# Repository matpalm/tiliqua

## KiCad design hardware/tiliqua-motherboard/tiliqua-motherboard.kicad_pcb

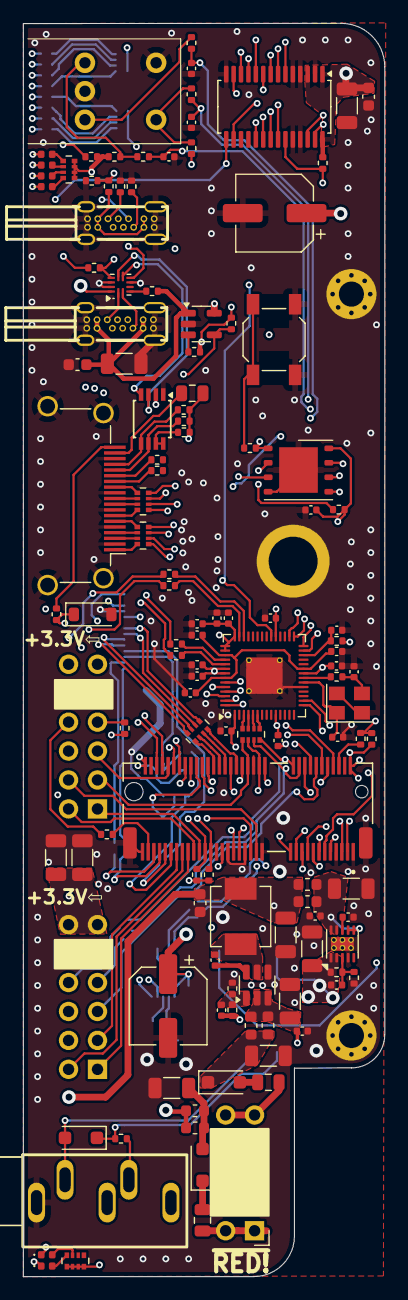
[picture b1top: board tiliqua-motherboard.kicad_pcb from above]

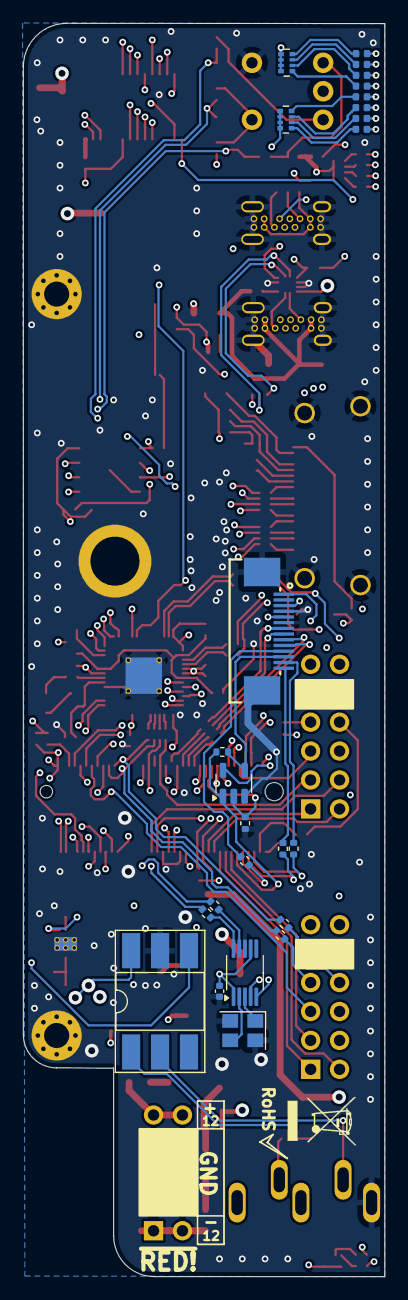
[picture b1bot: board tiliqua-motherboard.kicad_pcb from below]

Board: 6 copper layers, 31.7 x 110.0 mm, 153 parts (25 on the bottom side), 168 nets.

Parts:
C1, C2, C3, C4, C5, C6, C7, C8, C9, C10, C13, C14, C36: 0.1uF; C_0402_1005Metric
C11, C12: 2.2uF; C_0402_1005Metric
C15, C16: 15pF; C_0402_1005Metric
C17, C25, C28, C30: 100nF; C_0402_1005Metric
C18, C39, C40, C41: 10n; C_0402_1005Metric
C19, C20, C22, C23, C24, C26, C29, C32, C38, C42: 22uF; C_1206_3216Metric
C21, C33: 100uF/10V; CP_Elec_6.3x5.4
C27, C34, C43: 100nF; C_0603_1608Metric
C31: 100pF; C_0402_1005Metric
D1, D2, D3: 1N4007FL; D_SOD-123F
D4: 3V6; D_SOD-123
D5, D6, D7, D8, D13, D14, D16: LED 0402 GREEN; LED_0402_1005Metric
D9, D10, D11, D12, D17, D18, D20: LED 0402 RED; LED_0402_1005Metric
F1: 16V 350mA; Fuse_0805_2012Metric
F2: 15V 200mA; Fuse_0805_2012Metric
F3: 15V 50mA; Fuse_0805_2012Metric
H1, H2: MountingHole; MountingHole_2.2mm_M2_Pad_Via
H3: MountingHole; mounting_hole
J1: Conn_01x15; FFC_0.5-14P_CTXJ-H2.0_1
J2, J3: Conn_02x06_Top_Bottom; PinSocket_2x06_P2.54mm_Horizontal
J4: AUDIO-TH_PJ-325M
J5, J7: USB_C_Receptacle_USB2.0_14P; USB-C-TH_U264-141N-4BAC10
J6: CONN 2x5 P=2.54mm; PinHeader_2x05_P2.54mm_Horizontal
J8: MICROMOD-2222; TE_21992304
J10: DVI_GPDI; HDMI_A_Amphenol_10029449-x01xLF_Horizontal
L1, L2, L4, L5, L6, L7: FERRITE; L_0603_1608Metric
L3: 10uH 2A; L_Vishay_IHLP-2020
R1, R2, R9, R19, R25, R32: 4K7; R_0402_1005Metric
R3, R4, R13, R14, R21, R22, R23, R27, R28, R29, R30, R33, R45: 10K; R_0402_1005Metric
R5, R15: 1K; R_0402_1005Metric
R6, R7: 27R; R_0402_1005Metric
R8: 100R; R_0402_1005Metric
R10, R16: 220R; R_0402_1005Metric
R11, R12: 5.1K; R_0402_1005Metric
R17: 157K (158K); R_0402_1005Metric
R18: 30K; R_0402_1005Metric
R20: 900K (910K); R_0402_1005Metric
R24: 18K; R_0402_1005Metric
R26, R31: 549; R_0402_1005Metric
R34, R35, R36, R37, R38, R39, R40, R41, R47, R48, R49: 33R; R_0402_1005Metric
R42: 1K15; R_0402_1005Metric
R43: 3K57; R_0402_1005Metric
R44: 200K; R_0402_1005Metric
R46: 0R; R_0402_1005Metric
RN1, RN2, RN3, RN4, RN6, RN7: 220R; R_Array_Convex_4x0402
RN5, RN8: 33R; R_Array_Convex_4x0402
SW2: SW_Tactile_SPST; SW_SPST_SKQG_WithStem
SW3: RotaryEncoder_Switch; RotaryEncoder_Bourns_Horizontal_PEC09-2xxxF-Sxxxx
U2: RP2040(QFN-56_7x7mm_P0.4mm); QFN-56-1EP_7x7mm_P0.4mm_EP3.2x3.2mm_ThermalVias
U3: PCA9306DP; TSSOP-8_3x3mm_P0.65mm
U4: H11L1SR2M; DIP-6_W8.89mm_SMDSocket_LongPads
U5: AP63200WU; TSOT-23-6
U6: 74AUC1G79; SOT-23-5
U7: PCA9635 LED DRIVER; TSSOP-28_4.4x9.7mm_P0.65mm
U8: TUSB322I; Texas_X2QFN-12_1.6x1.6mm_P0.4mm
U9: AP2161W; SOT-23-5
U10: TPS7A91; Texas_S-PDSO-N10_EP1.2x2mm_ThermalVias
U11: Si5351A-B-GT; MSOP-10_3x3mm_P0.5mm
U12: W25Q128JVP; WSON-8-1EP_6x5mm_P1.27mm_EP3.4x4mm
Y1: Crystal_GND24_Small; Crystal_SMD_3225-4Pin_3.2x2.5mm
Y2: 25MHz AMB8G; Crystal_SMD_3225-4Pin_3.2x2.5mm

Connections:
+3V3: C1.2, C3.1, C4.1, C5.1, C6.1, C7.1, C8.1, C9.1, C10.1, C11.1, C18.2, C21.1, C22.1, C24.1, C32.1, C33.1, C36.1, C42.1, C43.1, J1.5, J2.6, J2.12, J3.6, J3.12, J8.2 (3.3V), J8.74 (3.3V), R1.2, R2.2, R3.1, R4.1, R13.1, R14.1, R15.2, R19.2, R21.1, R27.1, R32.2, R33.1, R43.1, RN1.1 (R1.1), RN1.2 (R2.1), RN1.3 (R3.1), RN1.4 (R4.1), RN2.1 (R1.1), RN2.2 (R2.1), RN2.3 (R3.1), RN2.4 (R4.1), RN3.1 (R1.1), RN3.2 (R2.1), RN3.3 (R3.1), RN3.4 (R4.1), RN4.1 (R1.1), RN4.2 (R2.1), RN4.3 (R3.1), RN4.4 (R4.1), U2.1 (IOVDD), U2.10 (IOVDD), U2.22 (IOVDD), U2.33 (IOVDD), U2.42 (IOVDD), U2.43 (ADC_AVDD), U2.44 (VREG_VIN), U2.48 (USB_VDD), U2.49 (IOVDD), U3.2 (VREF1), U4.6, U6.5 (VCC), U7.1 (A0), U7.3 (A2), U7.28 (VDD), U10.1 (OUT), U10.2 (OUT), U11.1 (VDD), U11.7 (VDDO), U12.8 (VCC)
+5V: C31.2, C34.1, C38.1, F3.2, L3.2, L4.2, L5.2, R9.2, R17.2, R25.2, R44.1, U8.12 (VDD), U9.5 (IN)
+12V: C23.1, C25.1, J1.3, L1.1, L6.2, U5.2 (EN), U5.3 (IN)
-12V: J1.1, L2.1, L7.2
/gpdi/CONN_CK+: J10.10 (CK+), RN7.2 (R2.1)
/gpdi/CONN_CK-: J10.12 (CK-), RN7.1 (R1.1)
/gpdi/CONN_D0+: J10.7 (D0+), RN7.4 (R4.1)
/gpdi/CONN_D0-: J10.9 (D0-), RN7.3 (R3.1)
/gpdi/CONN_D1+: J10.4 (D1+), RN6.2 (R2.1)
/gpdi/CONN_D1-: J10.6 (D1-), RN6.1 (R1.1)
/gpdi/CONN_D2+: J10.1 (D2+), RN6.4 (R4.1)
/gpdi/CONN_D2-: J10.3 (D2-), RN6.3 (R3.1)
/pmod_audio/PDN: J1.12, R46.1, U6.4 (Q)
/rp2040_jtag/I2C0_SCL: R40.1, U2.41 (GPIO29/ADC3/SPI1_CSn/UART0_RX/I2C0_SCL/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)
/rp2040_jtag/I2C0_SDA: R41.1, U2.40 (GPIO28/ADC2/SPI1_RX/UART0_TX/I2C0_SDA/P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)
/rp2040_jtag/RP2040_USB_D+: J5.A6 (D+), J5.B6 (D+), R7.1
/rp2040_jtag/RP2040_USB_D-: J5.A7 (D-), J5.B7 (D-), R6.1
/rp2040_jtag/RP2040_USB_VBUS: J5.A4 (VBUS), J5.A9 (VBUS), J5.B4 (VBUS), J5.B9 (VBUS), R23.2
/rp2040_jtag/SPI0_CSn: RN8.8 (R1.2), U2.3 (GPIO1/SPI0_CSn/UART0_RX/I2C0_SCL/PWM0_B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)
/rp2040_jtag/SPI0_RX: RN8.5 (R4.2), U2.6 (GPIO4/SPI0_RX/UART1_TX/I2C0_SDA/PWM2_A/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)
/rp2040_jtag/SPI0_SCK: RN8.7 (R2.2), U2.4 (GPIO2/SPI0_SCK/UART0_CTS/I2C1_SDA/PWM1_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)
/rp2040_jtag/SPI0_TX: RN8.6 (R3.2), U2.5 (GPIO3/SPI0_TX/UART0_RTS/I2C1_SCL/PWM1_B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)
/usbc/~USB_VBUS_FLG: R27.2, U9.3 (~FLG)
ECP5_M10_TDO: J8.23 (SWDIO), U2.28 (GPIO17/SPI0_CSn/UART0_RX/I2C0_SCL/PWM0_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)
ECP5_R11_TDI: J8.18 (D1/CAM_TRIG), U2.27 (GPIO16/SPI0_RX/UART0_TX/I2C0_SDA/PWM0_A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)
ECP5_T10_TCK: J8.10 (D0), U2.29 (GPIO18/SPI0_SCK/UART0_CTS/I2C1_SDA/PWM1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)
ECP5_T11_TMS: J8.21 (SWDCK), U2.30 (GPIO19/SPI0_TX/UART0_RTS/I2C1_SCL/PWM1_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)
ENC_A: C41.1, J8.8 (G11), R29.2
ENC_B: C40.1, J8.12 (I2C_SDA), R30.2
ENC_S: C39.1, J8.43 (CAN-TX), R22.2
EX1_1: J3.1, J8.55 (SPI_~CS)
EX1_2: J3.2, J8.38 (A1), RN8.1 (R1.1)
EX1_3: J3.3, J8.66 (SDIO_DATA1)
EX1_4: J8.41 (CAN-RX), R39.1
EX1_7: J3.7, J8.57 (SPI_SCK)
EX1_8: J3.8, J8.35 (USBHOST_D+)
EX1_9: J3.9, J8.34 (A0), RN8.2 (R2.1)
EX1_10: J8.73 (G5/BUS5), R38.2
EX2_1: J2.1, J8.59 (SPI_SDO)
EX2_2: J2.2, J8.63 (G10/ADC_D+/CAM_VSYNC)
EX2_3: J2.3, J8.14 (I2C_SCL)
EX2_4: J8.20 (RX2), R37.1, RN8.3 (R3.1)
EX2_7: J2.7, J8.61 (SPI_SDI)
EX2_8: J2.8, J8.15 (CTS1)
EX2_9: J2.9, J8.13 (RTS1)
EX2_10: J8.22 (TX2), R36.2, RN8.4 (R4.1)
FFC_BICK: J1.10, RN5.4 (R4.1)
FFC_LRCK: J1.9, RN5.3 (R3.1)
FFC_MCLK: J1.11, R49.2
FFC_PDN_CLK: J8.56 (AUD_OUT/CAM_MCLK), R45.2, U6.2 (C)
FFC_PDN_D: J8.65 (G9/ADC_D-/CAM_HSYNC), R46.2, U6.1 (D)
FFC_SCL: J1.14, R34.2
FFC_SDA: J1.13, R35.2
FFC_SDIN1: J1.7, RN5.1 (R1.1)
FFC_SDOUT1: J1.8, RN5.2 (R2.1)
GND: C1.1, C2.2, C3.2, C4.2, C5.2, C6.2, C7.2, C8.2, C9.2, C10.2, C11.2, C12.2, C13.2, C14.2, C15.2, C16.2, C17.2, C19.2, C20.1, C21.2, C22.2, C23.2, C24.2, C25.2, C26.2, C27.2, C28.2, C29.2, C32.2, C33.2, C34.2, C36.2, C38.2, C39.2, C40.2, C41.2, C42.2, C43.2, D4.2 (A), H1.1, H2.1, H3.1, J1.4, J1.6, J1.15, J2.5, J2.11, J3.5, J3.11, J4.G, J5.A1 (GND), J5.A12 (GND), J5.B1 (GND), J5.B12 (GND), J5.S1 (SHIELD), J6.3, J6.4, J6.5, J6.6, J6.7, J6.8, J7.A1 (GND), J7.A12 (GND), J7.B1 (GND), J7.B12 (GND), J7.S1 (SHIELD), J8.1 (GND), J8.7 (GND), J8.33 (GND), J8.36 (GND), J8.39 (GND), J8.45 (GND), J8.75 (GND), J8.S1 (GND), J8.S2 (GND), J10.2 (D2S), J10.5 (D1S), J10.8 (D0S), J10.11 (CKS), J10.17 (GND), J10.SH, R11.2, R12.2, R18.1, R24.1, R42.1, R45.1, SW2.1, SW3.C, SW3.S1, U2.19 (TESTEN(GND)), U2.57 (GND(EPAD)), U3.1 (GND), U4.5, U5.4 (GND), U6.3 (GND), U7.2 (A1), U7.4 (A3), U7.5 (A4), U7.14 (VSS), U7.24 (A5), U7.25 (A6), U8.5 (ADDR), U8.10 (GND), U8.11 (~EN), U9.2 (GND), U10.4 (GND), U10.11 (GND), U11.8 (GND), U12.4 (GND), U12.9 (GND), Y1.2, Y1.4, Y2.2, Y2.4
GPDI_CK+: J8.52 (AUD_LRCLK), RN7.7 (R2.2)
GPDI_CK-: J8.54 (AUD_IN/CAM_PCLK), RN7.8 (R1.2)
GPDI_D0+: J8.60 (SPI_SCK1/SDIO_CLK), RN7.5 (R4.2)
GPDI_D0-: J8.58 (AUD_MCLK), RN7.6 (R3.2)
GPDI_D1+: J8.62 (SPI_SDO1/SDIO_CMD), RN6.7 (R2.2)
GPDI_D1-: J8.64 (SPI_SDI1/SDIO_DATA0), RN6.8 (R1.2)
GPDI_D2+: J8.68 (SDIO_DATA2), RN6.5 (R4.2)
GPDI_D2-: J8.70 (SPI_~CS1/SDIO_DATA3), RN6.6 (R3.2)
GPDI_HPD: D4.1 (K), J8.37 (USBHOST_D-), R31.1
MIDI_RX: J8.6 (~RESET), R16.1
MOBO_I2C_SCL: J8.53 (I2C_SCL1), R1.1, R40.2, U3.3 (SCL1), U7.26 (SCL), U8.8 (SCL/OUT2), U11.4 (SCL)
MOBO_I2C_SDA: J8.51 (I2C_SDA1), R2.1, R41.2, U3.4 (SDA1), U7.27 (SDA), U8.7 (SDA/OUT1), U11.5 (SDA)
MOBO_LED_OE: J8.11 (~BOOT), R32.1, U7.23 (~OE)
unnamed: C15.1, R5.1, Y1.3
unnamed: D1.2 (A), J4.T, U4.2
unnamed: D1.1 (K), R10.2, U4.1
unnamed: D2.2 (A), F1.2
unnamed: C20.2, D2.1 (K), L1.2, L6.1
unnamed: C19.1, D3.2 (A), L2.2, L7.1
unnamed: D3.1 (K), F2.2
unnamed: D5.2 (A), RN1.8 (R1.2)
unnamed: D5.1 (K), U7.6 (LED0)
unnamed: D6.2 (A), RN2.8 (R1.2)
unnamed: D6.1 (K), U7.10 (LED4)
unnamed: D7.2 (A), RN3.8 (R1.2)
unnamed: D7.1 (K), U7.15 (LED8)
unnamed: D8.2 (A), RN4.8 (R1.2)
unnamed: D8.1 (K), U7.19 (LED12)
unnamed: D9.2 (A), RN1.7 (R2.2)
unnamed: D9.1 (K), U7.7 (LED1)
unnamed: D10.2 (A), RN2.7 (R2.2)
unnamed: D10.1 (K), U7.11 (LED5)
unnamed: D11.2 (A), RN3.7 (R2.2)
unnamed: D11.1 (K), U7.16 (LED9)
unnamed: D12.2 (A), RN4.7 (R2.2)
unnamed: D12.1 (K), U7.20 (LED13)
unnamed: D13.2 (A), RN1.6 (R3.2)
unnamed: D13.1 (K), U7.8 (LED2)
unnamed: D14.2 (A), RN2.6 (R3.2)
unnamed: D14.1 (K), U7.12 (LED6)
unnamed: D16.2 (A), RN4.6 (R3.2)
unnamed: D16.1 (K), U7.21 (LED14)
unnamed: D17.2 (A), RN1.5 (R4.2)
unnamed: D17.1 (K), U7.9 (LED3)
unnamed: D18.2 (A), RN2.5 (R4.2)
unnamed: D18.1 (K), U7.13 (LED7)
unnamed: D20.2 (A), RN4.5 (R4.2)
unnamed: D20.1 (K), U7.22 (LED15)
unnamed: J2.4, R37.2
unnamed: J2.10, R36.1
unnamed: J3.4, R39.2
unnamed: J3.10, R38.1
unnamed: J4.S, R10.1
unnamed: J5.A5 (CC1), R11.1
unnamed: J5.B5 (CC2), R12.1
unnamed: F2.1, J6.1, J6.2
unnamed: F1.1, J6.9, J6.10
unnamed: J7.A5 (CC1), U8.1 (CC1)
unnamed: J7.B5 (CC2), U8.2 (CC2)
unnamed: J8.50 (AUD_BCLK), RN5.5 (R4.2)
unnamed: J8.42 (G1/BUS1), RN5.8 (R1.2)
unnamed: J8.46 (G3/BUS3), RN5.7 (R2.2)
unnamed: J8.48 (G4/BUS4), RN5.6 (R3.2)
unnamed: J8.71 (G6/BUS6), R35.1
unnamed: J8.69 (G7/BUS7), R34.1
unnamed: J8.67 (G8), R49.1
unnamed: F3.1, J10.18 (+5V)
unnamed: J10.13 (CEC), R26.2
unnamed: J10.19 (HPD), R31.2
unnamed: J10.15 (SCL), R9.1, U3.6 (SCL2)
unnamed: J10.16 (SDA), R25.1, U3.5 (SDA2)
unnamed: J10.14 (UTILITY), R28.2
unnamed: R8.2, SW2.2
unnamed: R13.2, R22.1, SW3.S2
unnamed: R14.2, R29.1, SW3.B
unnamed: R15.1, R16.2, U4.4
unnamed: R21.2, R30.1, SW3.A
unnamed: R23.1, R24.2, U2.34 (GPIO22/SPI0_SCK/UART1_CTS/I2C1_SDA/PWM3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)
unnamed: C2.1, R4.2, U2.26 (RUN(RESET#))
unnamed: R6.2, U2.46 (USB_DM)
unnamed: R7.2, U2.47 (USB_DP)
unnamed: C12.1, C13.1, C14.1, U2.23 (DVDD), U2.45 (VREG_VOUT), U2.50 (DVDD)
unnamed: C16.1, U2.20 (XIN), Y1.1
unnamed: R5.2, U2.21 (XOUT)
unnamed: R44.2, U3.7 (VREF2), U3.8 (EN)
unnamed: C30.1, U5.6 (BST)
unnamed: C31.1, R17.1, R18.2, U5.1 (FB)
unnamed: C30.2, L3.1, U5.5 (SW)
unnamed: R20.2, U8.3 (VBUS_DET)
unnamed: C28.1, C29.1, L4.1, L5.1, U10.6 (SS_CTRL), U10.7 (EN), U10.9 (IN), U10.10 (IN)
unnamed: C18.1, R42.2, R43.2, U10.3 (FB)
unnamed: C17.1, U10.8 (NR/SS)
unnamed: R47.1, U11.10 (CLK0)
unnamed: R48.1, U11.9 (CLK1)
unnamed: U11.2 (XA), Y2.3
unnamed: U11.3 (XB), Y2.1
unnamed: U2.52 (QSPI_SCLK(Soft_GPIO)), U12.6 (CLK)
unnamed: U2.53 (QSPI_SD0(Soft_GPIO)), U12.5 (DI(IO0))
unnamed: U2.55 (QSPI_SD1(Soft_GPIO)), U12.2 (DO(IO1))
unnamed: U2.54 (QSPI_SD2(Soft_GPIO)), U12.3 (IO2)
unnamed: U2.51 (QSPI_SD3(Soft_GPIO)), U12.7 (IO3)
unnamed: R3.2, R8.1, U2.56 (QSPI_SS_N(Soft_GPIO)), U12.1 (~CS)
PLL_CLK0: J8.44 (G2/BUS2), R47.2
PLL_CLK1: J8.40 (G0/BUS0), R48.2
RP2040_UART0_RX: J8.17 (TX1), U2.16 (GPIO13/SPI1_CSn/UART0_RX/I2C0_SCL/PWM6_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)
RP2040_UART0_TX: J8.19 (RX1), U2.15 (GPIO12/SPI1_RX/UART0_TX/I2C0_SDA/PWM6_A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)
SC_USB0_D+: J7.A6 (D+), J7.B6 (D+), J8.3 (USB_D+)
SC_USB0_D-: J7.A7 (D-), J7.B7 (D-), J8.5 (USB_D-)
SC_USB0_ID: J8.16 (I2C_~INT), R19.1, U8.9 (ID)
SC_USB0_VBUS: C26.1, C27.1, J7.A4 (VBUS), J7.A9 (VBUS), J7.B4 (VBUS), J7.B9 (VBUS), J8.9 (USB_VIN), R20.1, U9.1 (OUT)
USB_INT: J8.47 (PWM1), U8.6 (~INT/OUT3)
USB_VBUS_EN: J8.32 (PWM0), R33.2, U9.4 (~EN)

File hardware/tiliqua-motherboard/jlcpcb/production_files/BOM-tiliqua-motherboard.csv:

Comment,Designator,Footprint,LCSC,Quantity
PCA9635 LED DRIVER,U7,TSSOP-28_4.4x9.7mm_P0.65mm,C110795,1
1K,"R15,R5",R_0402_1005Metric,C11702,2
2.2uF,"C11,C12",C_0402_1005Metric,C12530,2
33R,"RN5,RN8",R_Array_Convex_4x0402,C125323,2
PCA9306DP,U3,TSSOP-8_3x3mm_P0.65mm,C128835,1
22uF,"C19,C20,C22,C23,C24,C26,C29,C32,C38,C42",C_1206_3216Metric,C12891,10
33R,"R40,R41",R_0402_1005Metric,C138002,2
27R,"R6,R7",R_0402_1005Metric,C138021,2
100nF,"C27,C34,C43",C_0603_1608Metric,C14663,3
FERRITE,"L1,L2,L4,L5,L6,L7",L_0603_1608Metric,C14709,6
10n,"C18,C39,C40,C41",C_0402_1005Metric,C15195,4
100pF,C31,C_0402_1005Metric,C1546,1
15pF,"C15,C16",C_0402_1005Metric,C1548,2
3V6,D4,D_SOD-123,C173412,1
AP2161W,U9,SOT-23-5,C176957,1
W25Q128JVP,U12,WSON-8-1EP_6x5mm_P1.27mm_EP3.4x4mm,C190862,1
H11L1SR2M,U4,DIP-6_W8.89mm_SMDSocket_LongPads,C20082,1
SW_Tactile_SPST,SW2,SW_SPST_SKQG_WithStem,C202424,1
RP2040(QFN-56_7x7mm_P0.4mm),U2,QFN-56-1EP_7x7mm_P0.4mm_EP3.2x3.2mm_ThermalVias,C2040,1
Crystal_GND24_Small,Y1,Crystal_SMD_3225-4Pin_3.2x2.5mm,C20625731,1
AP63200WU,U5,TSOT-23-6,C2071868,1
MountingHole,H3,mounting_hole,C22368605,1
100R,R8,R_0402_1005Metric,C25076,1
220R,"R10,R16",R_0402_1005Metric,C25091,2
33R,"R34,R35,R36,R37,R38,R39,R47,R48,R49",R_0402_1005Metric,C25105,9
LED 0402 RED,"D10,D11,D12,D17,D18,D20,D9",LED_0402_1005Metric,C25503345,7
10K,"R13,R14,R21,R22,R23,R27,R29,R3,R30,R33,R4,R45",R_0402_1005Metric,C25744,12
18K,R24,R_0402_1005Metric,C25762,1
200K,R44,R_0402_1005Metric,C25764,1
30K,R18,R_0402_1005Metric,C25776,1
900K (910K),R20,R_0402_1005Metric,C25800,1
4K7,"R1,R2,R25,R32,R9",R_0402_1005Metric,C25900,5
5.1K,"R11,R12",R_0402_1005Metric,C25905,2
TUSB322I,U8,Texas_X2QFN-12_1.6x1.6mm_P0.4mm,C2674422,1
3K57,R43,R_0402_1005Metric,C270609,1
74AUC1G79,U6,SOT-23-5,C2869706,1
TPS7A91,U10,Texas_S-PDSO-N10_EP1.2x2mm_ThermalVias,C2878140,1
~,J4,AUDIO-TH_PJ-325M,C2884942,1
Conn_02x06_Top_Bottom,"J2,J3",PinSocket_2x06_P2.54mm_Horizontal,C2897426,2
1K15,R42,R_0402_1005Metric,C29401,1
MICROMOD-2222,J8,TE_21992304,C2977809,1
0.1uF,"C1,C10,C13,C14,C17,C2,C25,C28,C3,C30,C36,C4,C5,C6,C7,C8,C9",C_0402_1005Metric,C307331,17
220R,"RN1,RN2,RN3,RN4,RN6,RN7",R_Array_Convex_4x0402,C326868,6
DVI_GPDI,J10,HDMI_A_Amphenol_10029449-x01xLF_Horizontal,C428493,1
549,R31,R_0402_1005Metric,C474081,1
CONN 2x5 P=2.54mm,J6,PinHeader_2x05_P2.54mm_Horizontal,C492433,1
1N4007FL,"D1,D2,D3",D_SOD-123F,C493190,3
Si5351A-B-GT,U11,MSOP-10_3x3mm_P0.5mm,C504891,1
Conn_01x15,J1,FFC_0.5-14P_CTXJ-H2.0_1,C5373472,1
25MHz AMB8G,Y2,Crystal_SMD_3225-4Pin_3.2x2.5mm,C596913,1
USB_C_Receptacle_USB2.0_14P,"J5,J7",USB-C-TH_U264-141N-4BAC10,C692526,2
10uH 2A,L3,L_Vishay_IHLP-2020,C844996,1
157K (158K),R17,R_0402_1005Metric,C861679,1
15V 50mA,F3,Fuse_0805_2012Metric,C883096,1
15V 200mA,F2,Fuse_0805_2012Metric,C883103,1
16V 350mA,F1,Fuse_0805_2012Metric,C883107,1
100uF/10V,"C21,C33",CP_Elec_6.3x5.4,C88795,2
LED 0402 GREEN,"D13,D14,D16,D5,D6,D7,D8",LED_0402_1005Metric,C965793,7
RotaryEncoder_Switch,,RotaryEncoder_Bourns_Horizontal_PEC09-2xxxF-Sxxxx,,0

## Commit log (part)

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2025-01-04 * cleaner DVI routing / USB2 layerswap
2025-01-04 * update DNP entries, add nlnet logo
2025-01-04 * apf.audio + nlnet on panel
2025-01-05 * fab 05.01.24
2025-01-06 compute spread spectrum constants w/ cargo test --target=x86_64-unknown-linux-gnu -- --nocapture
2025-01-06 add calculation test
2025-01-08 second output ok
2025-01-08 streamline fwloc
2025-01-08 bitstream archive
2025-01-08 crc and version on py side
2025-01-08 names and patterns
2025-01-08 check exceeding slot
2025-01-08 jump works, crc and crc err works
2025-01-08 support multiple regions, rs side not done
2025-01-08 build r2 and r3 matrix, attach all in one file
2025-01-08 cimatrix
2025-01-08 brief and default offset calcs
2025-01-08 support null psram dst in bl
2025-01-08 remove unnecessary override
2025-01-08 fixup paths
2025-01-08 fix simulation
2025-01-08 add flasher, works
2025-01-08 overlap protection
2025-01-08 manifest generation
2025-01-08 update flashing instructions emitted by cli
2025-01-08 move manifest parse to lib, add test
2025-01-08 run from psram works in sim
2025-01-08 update docs
2025-01-08 default psram
2025-01-08 start copying
2025-01-08 compiles, no idea if it works
2025-01-08 fix sim compilation
2025-01-18 bootloader/build: bitstream archives, bootloader manifests and flashing tool (#75)
    * All projects now generate a 'bitstream archive', which is a .tar.gz archive that contains a bitstream, (optionally) a firmware image and (optionally) extra resources. A 'manifest' is also included 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
    * A new binary target, pdm flash <archive> --slot X can be used to flash bitstream archives to any of the 8 Tiliqua slots.
    * Because firmware images now run from PSRAM instead of SPI flash (XiP), any project can be located in any slot, even if it contains a firmware image
2025-01-18 hw/r3: update docs for R3 hardware (R2 still the default)
2025-01-18 polysyn: add optional USB MIDI host (#76)
    - Add USB screen to `polysyn` menu for enabling MIDI HOST (disconnects TRS MIDI if enabled)
    - Correct config ID and endpoint ID can be set in menu, but must currently be manually checked (and set) by looking at the USB device descriptor (e.g. using `lsusb`).
2025-01-18 example/sid: add `sid` example (#77)
    - Add `sid` emulation demo to example suite and rebase on `main` (it's been hanging around in an abandoned branch for a while and deserves to live here).
2025-01-18 flash: add 'status' command for dumping manifest status (#78)
    - Modify `pdm flash` command to have `archive` and `status` subcommands.
    - Now, `pdm flash archive <bitstream.tar.gz>` is used for flashing bitstreams to Tiliqua slots.
    - A new `pdm flash status` command is added for dumping the contents of each manifest in every slot (to see what's currently programmed to the Tiliqua).
2025-01-19 flash: improve bootloader bootstrap documentation (#79)
2026-02-08 pyproject: bump (update guh, improves MIDI host enumeration reliability)
2026-02-22 hal/spiflash: write_enable is needed before every write op
2026-02-22 dsp/delay_line: bypass ZDELAY state when write_triggers_read=False
2026-02-22 periph/grain_player: implement scrub mode, linear interpolation between taps
2026-02-22 lib/draw: add helper for drawing CV waveforms, so we have 'lines' or 'peaks'
2026-02-26 top/sampler: switch from 3->1 shared delayline, hook up scrub lines
2026-02-26 top/sampler: update fw for 3->1 delaylines, and: * add support for new GrainPlayer modes * add support for spiflash save/load of the delayline with progress * add line/peak draw modes * draw full buf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
2026-02-28 top/sampler: fix OneShot docstring (retrigger mid-grain)
2026-03-02 macro_osc: fix ypos out/aux
2026-03-02 eurorack_pmod/raster/xbeam: improve support for >16-bit samples: - Split ASQ (audio sample) and PSQ (plotting sample) - So we can have wide audio samples without touching plotting width. - Permit ASQ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
2026-03-02 scripts/bootstrap: add --erase-option-storage for sampler
2026-03-02 xbeam/scope: add /d or d as suffix for 'per-division' options, swap SCOPE1/SCOPE2 pages
2026-03-02 selftest/pmod: support arbitrary ASQ width in selftest and calibration readback * also allow up to +/- 10V output stimuli (ADC tops out there, DAC around +/- 9V)
2026-03-02 video/overlay: add ability to chain beamracing overlay after the framebuffer
2026-03-02 xbeam/scope: add n_channels option to scope
2026-03-02 top/beamrace: fix for new DVIPixel API
2026-03-04 docs/tlq_expander: add note on experimental firmware for 12x12 usb audio
2026-03-07 midi: add sustain pedal support
2026-03-08 midi: implement voice_active cull inhibit
2026-03-08 dsp/voice_block: add (squashed) + simple test
2026-03-08 top/polysyn: rewrite to use voiceblock, add hal
2026-03-08 dsp/block: add BlockMerge utility
2026-03-08 opts/polysyn: cc mappings, lfo * add cc mapping in opts library * top/polysyn: move reso to VOICE page * top/polysyn: add sine lfo, final cc mappings
2026-03-08 top/cli: print what's causing -d suffix if repo is dirty
2026-03-08 ci: ignore .env.toolchain changes for release tagging purposes
2026-03-09 scripts/build_bitstreams_no_soc: build both 1280x720 and 720x720 bitstreams for static modelines
2026-03-09 scripts/build_bitstreams_no_soc: build second set of static modeline bitstreams after the first set
2026-03-09 top/beamrace: fix --name cli override
2026-03-27 dsp/block: add BlockSelect utility for trimming blocks
2026-03-27 dsp/BlockLPF: make smoothing constant a constructor argument
2026-03-27 midi: add CCFilter for latching CCs at audio clock rate
2026-03-27 top/dsp: add MidiMatrixMixer with CC smoothing and saturation
2026-03-27 dsp/matrix: fix testcase (saturates now)
2026-03-28 top/dsp/mmm: switch from tanh to piecewise saturation
2026-03-28 top/dsp/mmm: add x^2 audio taper on cc ins
2026-03-28 top/dsp/mmm: update ccs
2026-03-28 dsp/mmm/BlockLPF: add 1-2 extra LSBs
2026-03-29 rs/opts/polysyn: speed up MIDI CC injection
2026-03-29 top/polysyn: expose MIDI clock on output 1
2026-03-29 top/polysyn: convert in1/in2 to bipolar offsets
2026-03-29 top/polysyn: update docstring, use cc 80 for palette
2026-03-29 rs/lib/palette: compute all palettes statically for speed
2026-03-29 dsp/oneshot: fix ramp reset on wide PSQ/ASQ
2026-04-03 top/xbeam: add TRS MIDI CC control
2026-04-03 top/polysyn: remap, document polysyn CCs
2026-04-03 top/polysyn: share multipliers in output stage
2026-04-03 midi/matrixmix: remap CCs, improve docstring
2026-04-03 tiliqua_soc/docs: fix duplicate docstrings
2026-04-03 dsp/misc: increase GateDetector threshold 2V->4V
    prevents sampler bitstream sometimes false-triggering
2026-04-06 docs/quickstart: improve docs on updates
2026-04-12 top/xbeam/persist: unify decay/persist, reduce flickering
2026-04-21 mark "52Pi 7 Inch" modeline config as non standard
2026-04-22 game of life beamracer for learning.
2026-04-22 tick game forward on rising edge of in0
2026-04-22 random flip from in1
2026-04-22 init with glider
2026-04-22 working, but only screen updates at crossing zero, grid is progressing faster?
2026-04-22 with latch and vsync
2026-04-22 mode line config for the "52Pi 7 Inch HDMI IPS Display" (#168)
    * mode line config for the "52Pi 7 Inch HDMI IPS Display"
    * mark "52Pi 7 Inch" modeline config as non standard
2026-04-22 dont use an oscillator and zero crossing; use a direct voltage added to a counter
2026-04-22 if CV is -ve, use 0
2026-04-25 include r_pentomino
2026-04-25 use dsp example as a template for building
2026-05-04 hack mirror back in to prove connection
2026-05-04 wire up top to qb_network
2026-05-06 3 layer version
2026-05-06 remove debug outs
2026-05-06 general QbNetwork working
2026-05-07 add filtering to output
2026-05-07 check $RUN
2026-05-13 4d input quadrature version
2026-05-13 send red channel out on ch0
2026-05-13 feedback kinda working. sync signal sent out4 -> in4. image send out3 -> in3.
2026-05-13 switch from RGBRGB to RRGGBB
2026-05-13 more tweaking of sync vs img
2026-05-13 remove YUV, doesnt work?
2026-05-14 more hacking
2026-05-14 getting even messier :/ need to ditch BeamRaceTop and refactor to single elaboratable?
2026-05-14 try to clean up
2026-05-16 wip spi test
2026-05-17 rasp pi capture
2026-05-17 wire in SPI upload
2026-05-17 simpler py server
2026-05-17 mo cleanup
2026-05-17 remove debug
2026-05-17 remove more debug
2026-05-17 switch in1 to be an alpha blend from raw loopback to feedback
2026-05-17 make python server a service
2026-05-17 tweak
2026-05-27 normal cosine estimator
2026-05-27 wire in cosine estimation. cdcc fdd603ab
2026-06-09 first cut; ctrl mode; pad c# start/stop, pad c playback
2026-06-09 decimate from 48kHz to 14.4 in prep for paula hookup
2026-06-09 add a second sample; in1->out1 controlled by pads d# and d
2026-06-09 externalise some config
2026-06-10 config tweaks
2026-06-10 include err diffusing dither
2026-06-10 switch from one shot to playback toggle
2026-06-10 scrappy led-like 2 stage lpf
2026-06-10 include minimig as dep for submodules
2026-06-10 move lpf into sample
2026-06-10 minimal wiring in of paula and fake_agnus
2026-06-10 wip paula_audio wrapper
2026-06-10 two steps back, fixed triangle wave passed through paula
2026-06-10 wire AUD0DAT directly from in0
2026-06-10 switch for sanity between fake dma vs real path
2026-06-10 more wip; USE_FAKE_AGNUS_DMA bool
2026-06-10 dma feed; remvoe debug delay
2026-06-10 rewire _back_ to Sample
2026-06-10 back to just in0 -> paula -> out0
2026-06-10 refactoring / comments
2026-06-10 wire back in second channel
2026-06-10 use array of Channel, not channel0, 1 etc
2026-06-10 move midi processing into seperate module
2026-06-10 refactor midi config
2026-06-10 plumb enc1 to ch0 vol
2026-06-10 changing way encoders map live to registers
2026-06-11 use const AUD0VOL==64 value at startup
2026-06-11 regress to single shot record / playback for debugging
2026-06-11 back to toggling record/playback
2026-06-11 zero crossing
2026-06-11 tuning AUD0PER encoder range; something wrong in that we still can't pitch up
2026-06-12 capture 1s of audio from in0 and playback at x1 speed, then x4 then 1/4
2026-06-12 fuck it, remove DMA limit and drive by CPU. much higher range and no "official" cheat
2026-06-12 rewire bsp enc 3 -> aud0vol
2026-06-12 wire bsp enc2 to aud0per
2026-06-12 start stop playback
2026-06-12 fix record/playback state machine
2026-06-12 8bit sample -> x64 volume just signal level. add +6db boost back
2026-06-12 vendor the minimig paula_audio pieces so we can expose ADKCON. this cant be the right way?
2026-06-12 wire in ch1
2026-06-12 remove USE_CPU_FEED hack
2026-06-12 increase mod depth for ATPER0
2026-06-12 swap range for AUDxPER so CW is higher pitch
2026-06-12 add ch2
2026-06-13 generalise midi config more
2026-06-13 wire in AUDxLEN handling
2026-06-13 cleanup
2026-06-13 fake_agni
2026-06-13 more seams
2026-06-13 reset all known AUD registers
2026-06-13 can unify register list now
2026-06-13 remove stale code
2026-06-13 wire in ch3
2026-06-13 just init ADKCON as 0
2026-06-13 include dither from v1. not used, keep for later if required
2026-06-13 minimig is gpl3, so this is too
2026-06-13 v2 replaces v1
2026-06-13 more cleanup
2026-06-13 renamed v2 back to implied v1
2026-06-13 comments
2026-06-14 fix bug re: midi structure
2026-06-14 explicit handling of lin/exp params
2026-06-14 fix capture rate bug
2026-06-14 stray from "real" paula to make FM & AM more audio based
2026-06-14 emit L+R on out2
2026-06-16 switch AUDLEN to log add fake AUDxSTART, ( just commented out for now, buggy ) add toggle one shot move midi stuff into midi.py switch to PSRAM. bugs?
2026-06-21 wire in mirror example
2026-06-21 diy benjolin. very chaotic :/
2026-06-22 match cdcc 7c59a63; psram for act caches
